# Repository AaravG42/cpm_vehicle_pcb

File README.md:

View this project on [CADLAB.io](https://cadlab.io/project/29694). 

# cpm_vehicle_pcb

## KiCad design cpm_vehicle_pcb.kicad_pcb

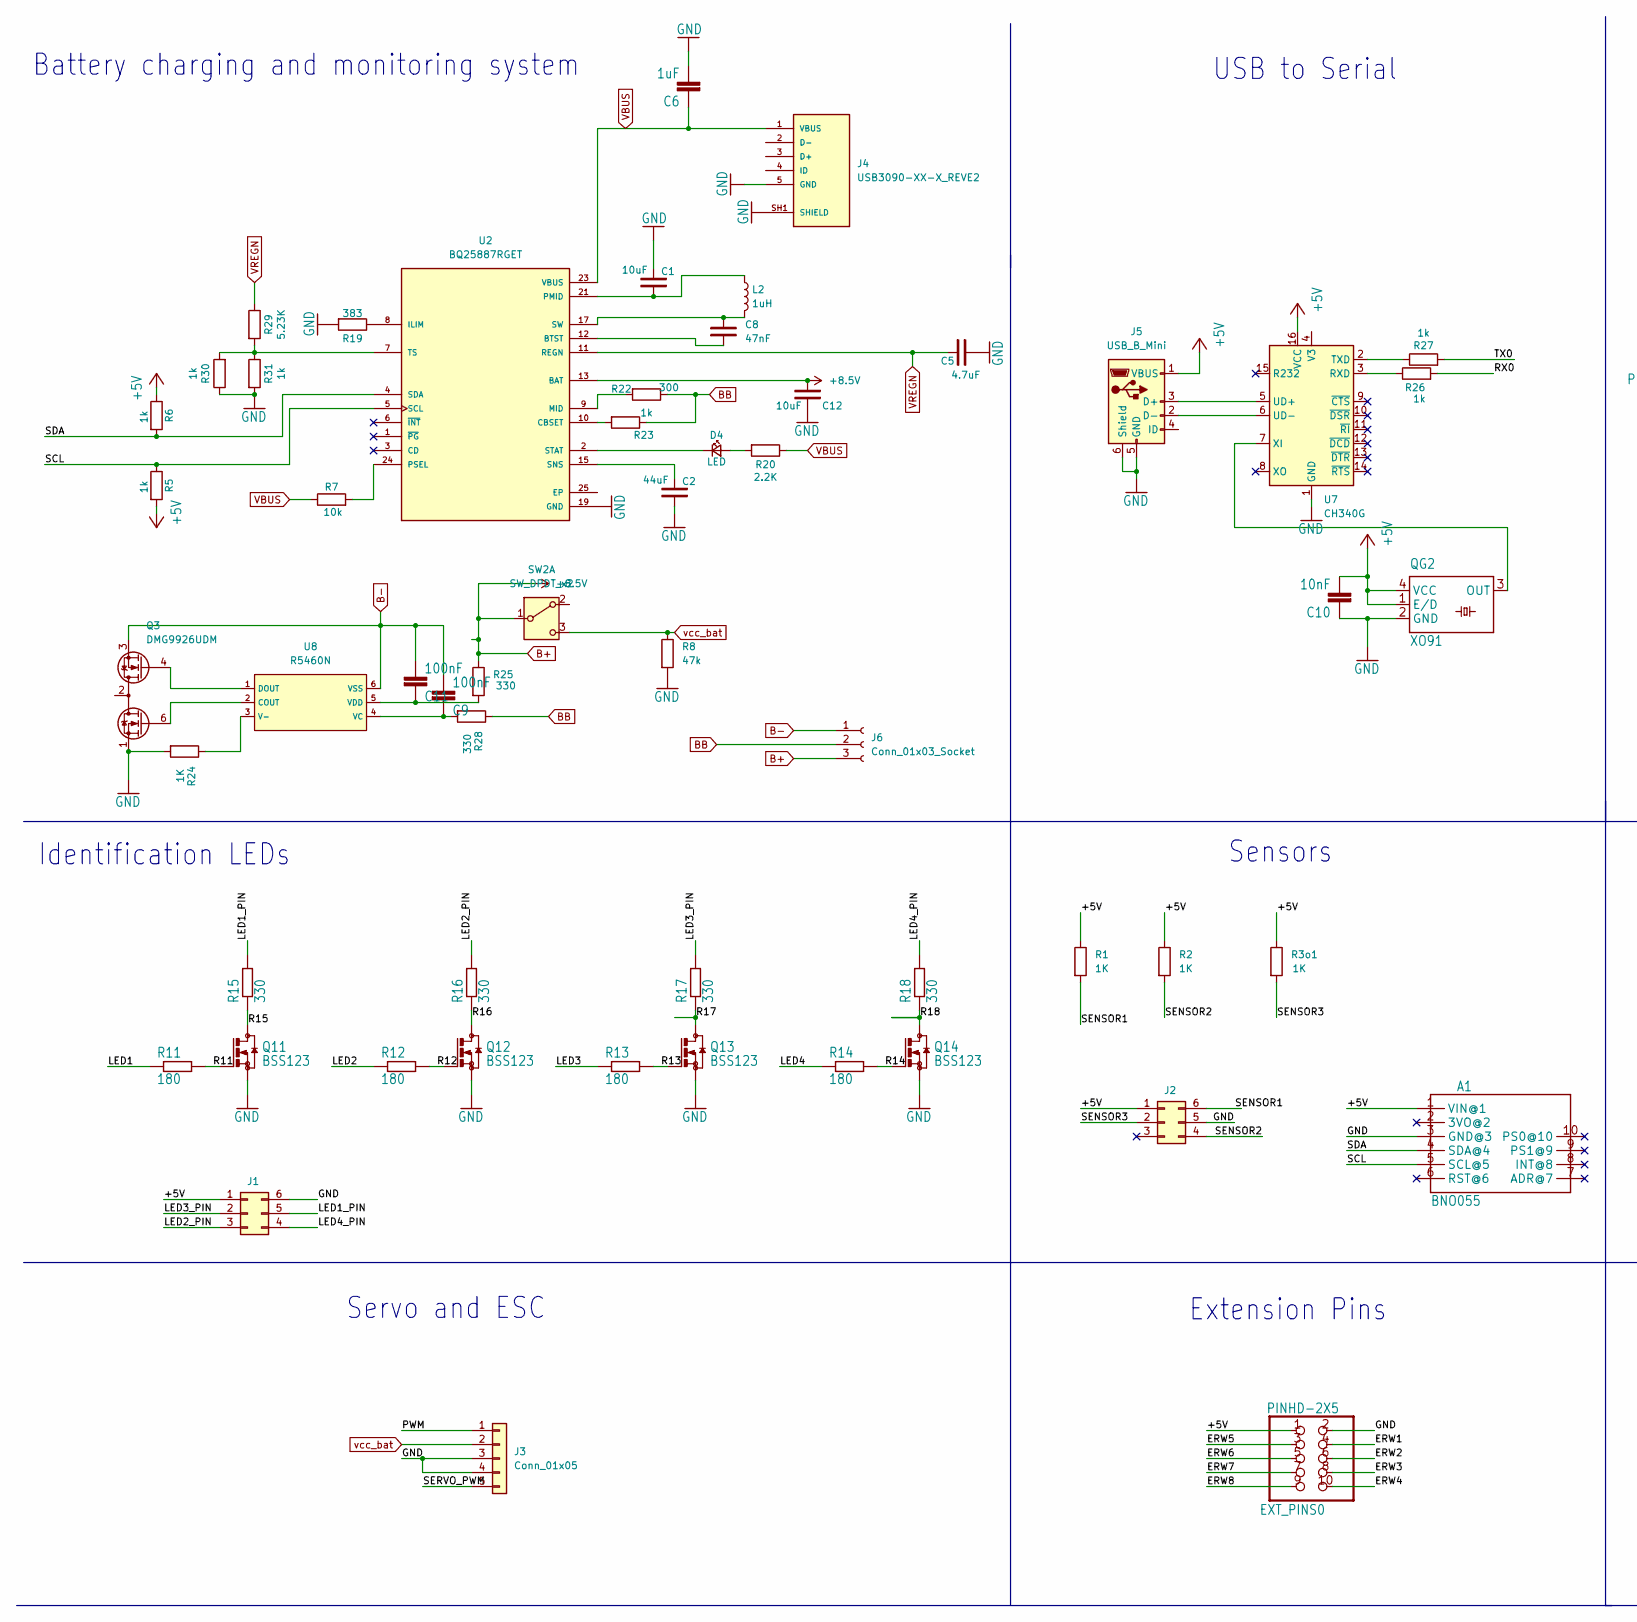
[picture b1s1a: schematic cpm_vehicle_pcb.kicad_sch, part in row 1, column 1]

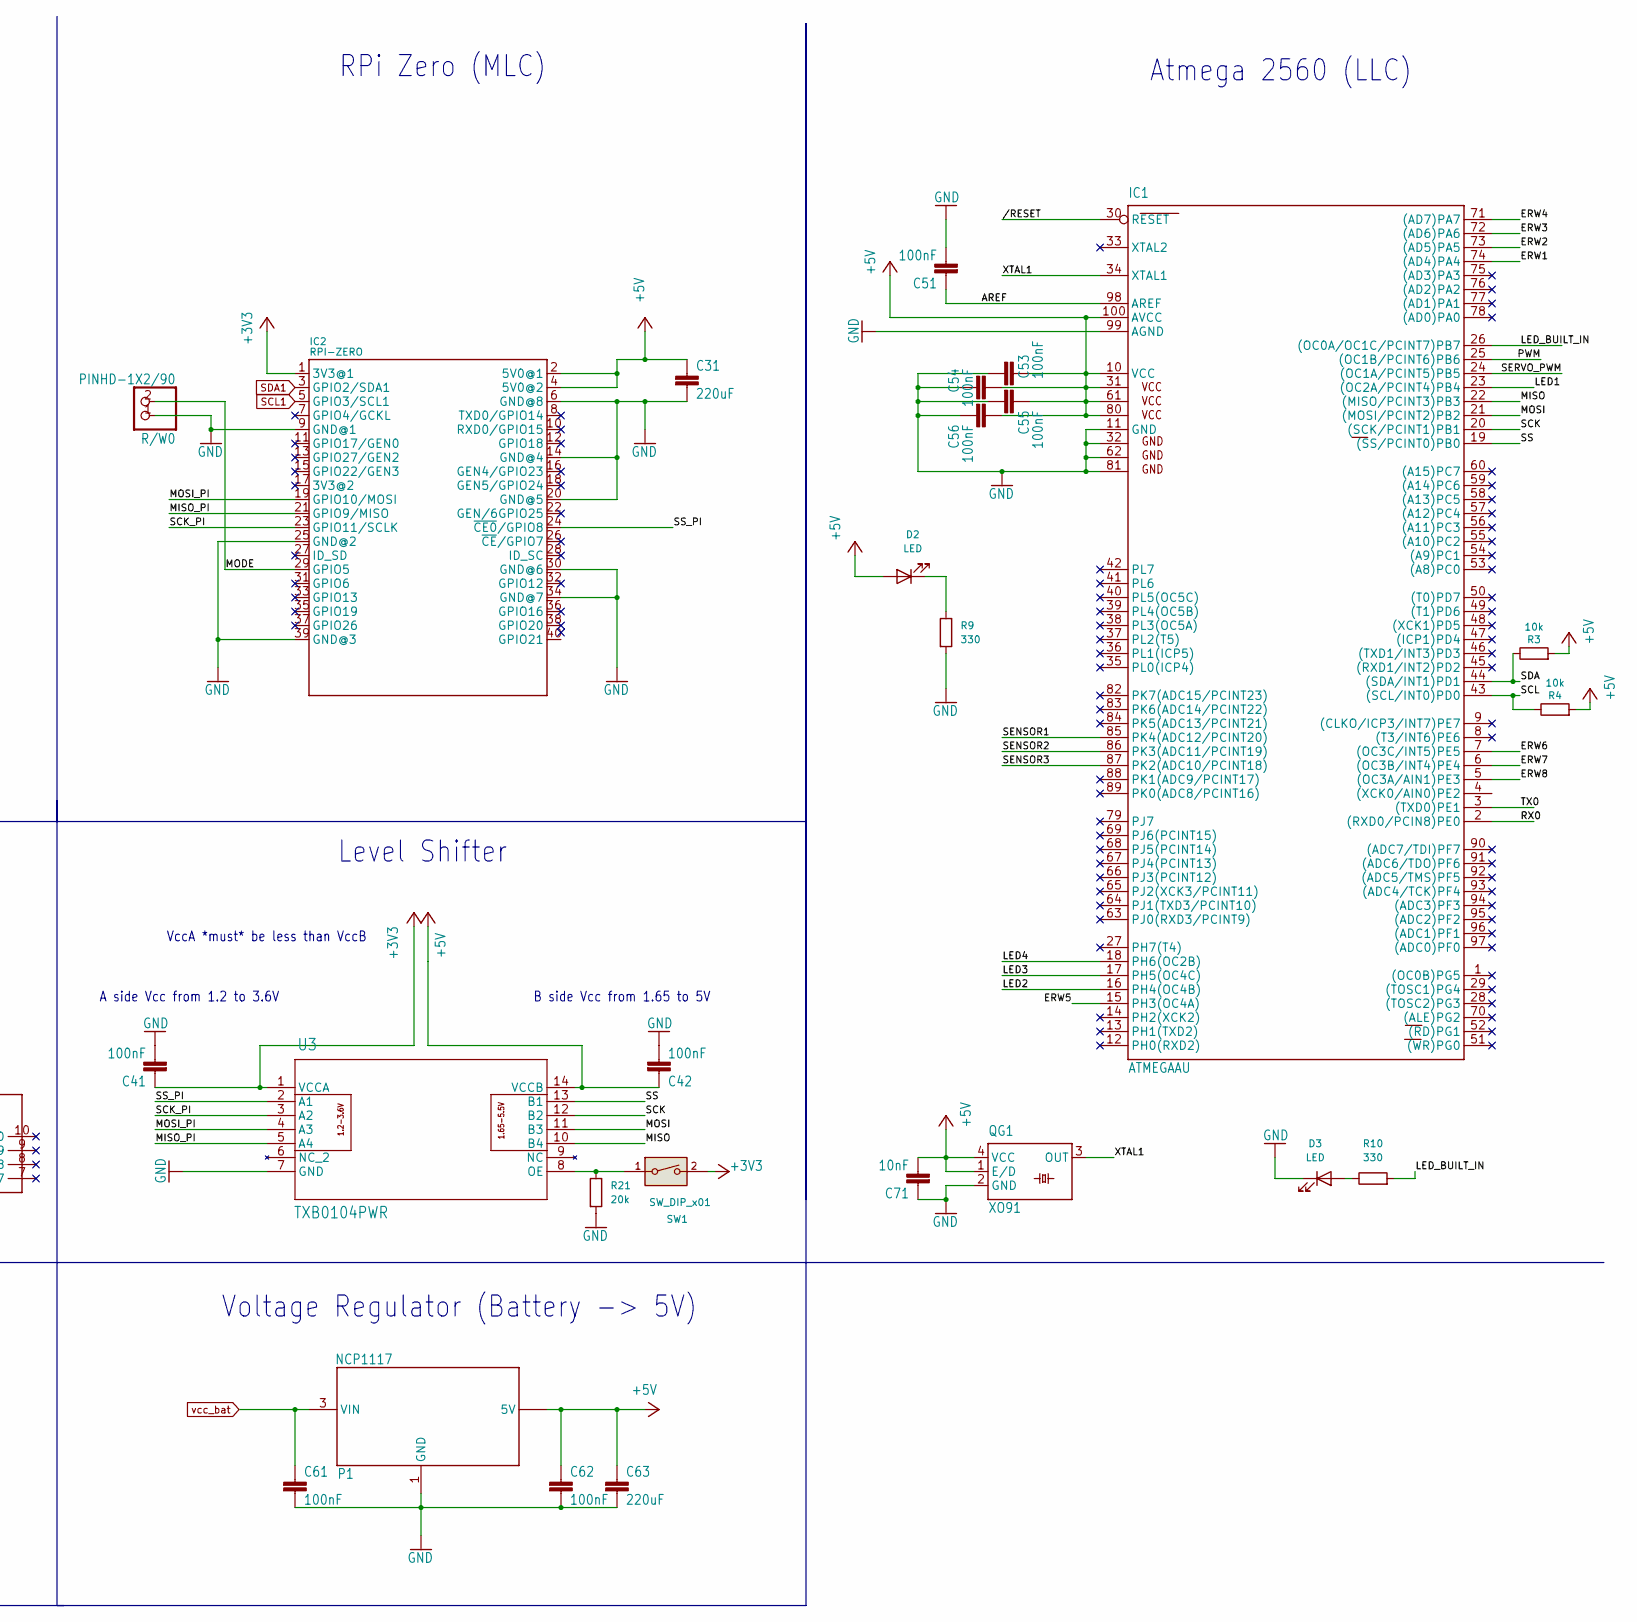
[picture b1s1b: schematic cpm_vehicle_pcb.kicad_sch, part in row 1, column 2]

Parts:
A1: BNO055; BNO055_IMU
C1, C12: 10uF; C0805_10681391
C2: 44uF; C0805_10681391
C5: 4.7uF; C0805_10681391
C6: 1uF; C0805_10681391
C8: 47nF; C0805_10681391
C9, C11, C41, C42, C51, C53, C54, C55, C56, C61, C62: 100nF; C0805_10681391
C10, C71: 10nF; C0805_10681391
C31, C63: 220uF; C_1206_3216Metric
D2, D3, D4: LED; LED_0805_2012Metric
EXT_PINS0: PINHD-2X5; 2X05_EXT_PINS
IC1: ATMEGAAU; TQFP100_atmega2560
IC2: RPI-ZERO; rpi_zero_w
J1, J2: Conn_02x03_Counter_Clockwise; HARWIN_M20-9980346
J3: Conn_01x05; PinHeader_1x05_P2.54mm_Horizontal
J4: USB3090-XX-X_REVE2; GCT_USB3090-XX-X_REVE2; PARTREV E2
J5: USB_B_Mini; USB_Mini-B_AdamTech_MUSB-B5-S-VT-TSMT-1_SMD_Vertical
J6: Conn_01x03_Socket; PinSocket_1x03_P2.54mm_Horizontal
L2: 1uH; L_7.3x7.3_H3.5
P1: NCP1117; SOT223_ncp1117
Q3: DMG9926UDM; SOT-23-6
Q11, Q12, Q13, Q14: BSS123; SOT23_NMOS
QG1, QG2: XO91; SM77H_crystal_oscillator
R1, R2, R3o1, R24: 1K; R_0603_1608Metric
R3, R4, R7: 10k; R_0603_1608Metric
R5, R6, R23, R26, R27, R30, R31: 1k; R_0603_1608Metric
R8: 47k; R_0603_1608Metric
R9, R10, R15, R16, R17, R18, R25, R28: 330; R_0603_1608Metric
R11, R12, R13, R14: 180; R_0603_1608Metric
R19: 383; R_0603_1608Metric
R20: 2.2K; R_0603_1608Metric
R21: 20k; R_0603_1608Metric
R22: 300; R_0603_1608Metric
R29: 5.23K; R_0603_1608Metric
R/W0: PINHD-1X2/90; 1X02_90_rpi
SW1: SW_DIP_x01; SW_DIP_SPSTx01_Slide_9.78x4.72mm_W8.61mm_P2.54mm
SW2: SW_DPDT_x2; SW_Slide-03_Wuerth-WS-SLTV_10x2.5x6.4_P2.54mm
U2: BQ25887RGET; QFN50P400X400X100-25N; PARTREV B
U3: TXB0104PWR
U7: CH340G; SOIC-16_3.9x9.9mm_P1.27mm
U8: R5460N; SOT-23-6_L2.9-W1.6-P0.95-LS2.8-BL; Part TP4057-42-SOT26-R; LCSC C12044

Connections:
+3V3: C41.1, IC2.1 (3V3@1), SW1.2, U3.1 (VCCA)
+5V: A1.1 (VIN@1), C10.2, C31.1, C42.1, C53.1, C54.1, C55.1, C56.1, C62.1, C63.1, C71.2, D2.2 (A), EXT_PINS0.1, IC1.10 (VCC), IC1.31 (VCC1), IC1.61 (VCC2), IC1.80 (VCC3), IC1.100 (AVCC), IC2.2 (5V0@1), IC2.4 (5V0@2), J1.1, J2.1, J5.1 (VBUS), P1.2 (5V), P1.4 (5V), QG1.1 (E/D), QG1.4 (VCC), QG2.1 (E/D), QG2.4 (VCC), R1.1, R2.1, R3.2, R3o1.1, R4.2, R5.2, R6.1, U3.14 (VCCB), U7.16 (VCC)
/AREF: C51.1, IC1.98 (AREF)
/ERW1: EXT_PINS0.4, IC1.74 ((AD4)PA4)
/ERW2: EXT_PINS0.6, IC1.73 ((AD5)PA5)
/ERW3: EXT_PINS0.8, IC1.72 ((AD6)PA6)
/ERW4: EXT_PINS0.10, IC1.71 ((AD7)PA7)
/ERW5: EXT_PINS0.3, IC1.15 (PH3(OC4A))
/ERW6: EXT_PINS0.5, IC1.7 ((OC3C/INT5)PE5)
/ERW7: EXT_PINS0.7, IC1.6 ((OC3B/INT4)PE4)
/ERW8: EXT_PINS0.9, IC1.5 ((OC3A/AIN1)PE3)
/LED1: IC1.23 ((OC2A/PCINT4)PB4), R11.1
/LED1_PIN: J1.5, R15.2
/LED2: IC1.16 (PH4(OC4B)), R12.1
/LED2_PIN: J1.3, R16.2
/LED3: IC1.17 (PH5(OC4C)), R13.1
/LED3_PIN: J1.2, R17.2
/LED4: IC1.18 (PH6(OC2B)), R14.1
/LED4_PIN: J1.4, R18.2
/LED_BUILT_IN: IC1.26 ((OC0A/OC1C/PCINT7)PB7), R10.2
/MISO: IC1.22 ((MISO/PCINT3)PB3), U3.10 (B4)
/MISO_PI: IC2.21 (GPIO9/MISO), U3.5 (A4)
/MODE: IC2.29 (GPIO5), R/W0.2
/MOSI: IC1.21 ((MOSI/PCINT2)PB2), U3.11 (B3)
/MOSI_PI: IC2.19 (GPIO10/MOSI), U3.4 (A3)
/PWM: IC1.25 ((OC1B/PCINT6)PB6), J3.1
/R11: Q11.1 (G), R11.2
/R12: Q12.1 (G), R12.2
/R13: Q13.1 (G), R13.2
/R14: Q14.1 (G), R14.2
/R15: Q11.3 (D), R15.1
/R16: Q12.3 (D), R16.1
/R17: Q13.3 (D), R17.1
/R18: Q14.3 (D), R18.1
/RX0: IC1.2 ((RXD0/PCIN8)PE0), R26.2
/SCK: IC1.20 ((SCK/PCINT1)PB1), U3.12 (B2)
/SCK_PI: IC2.23 (GPIO11/SCLK), U3.3 (A2)
/SCL: A1.5 (SCL@5), IC1.43 ((SCL/INT0)PD0), R4.1, R5.1, U2.5 (SCL)
/SDA: A1.4 (SDA@4), IC1.44 ((SDA/INT1)PD1), R3.1, R6.2, U2.4 (SDA)
/SENSOR1: IC1.85 (PK4(ADC12/PCINT20)), J2.6, R1.2
/SENSOR2: IC1.86 (PK3(ADC11/PCINT19)), J2.4, R2.2
/SENSOR3: IC1.87 (PK2(ADC10/PCINT18)), J2.2, R3o1.2
/SERVO_PWM: IC1.24 ((OC1A/PCINT5)PB5), J3.5
/SS: IC1.19 ((SS/PCINT0)PB0), U3.13 (B1)
/SS_PI: IC2.24 (~CE0/GPIO8), U3.2 (A1)
/TX0: IC1.3 ((TXD0)PE1), R27.2
/XTAL1: IC1.34 (XTAL1), QG1.3 (OUT)
//RESET: IC1.30 (RESET)
B+: C12.1, J6.3, R25.1, SW2.1 (B), U2.13 (BAT), U2.14 (BAT)
B-: C9.2, C11.2, J6.1, Q3.3 (S2), U8.6 (VSS)
BB: J6.2, R22.1, R23.1, R28.1
GND: A1.3 (GND@3), C1.1, C2.2, C5.2, C6.2, C10.1, C12.2, C31.2, C41.2, C42.2, C51.2, C53.2, C54.2, C55.2, C56.2, C61.2, C62.2, C63.2, C71.1, D3.1 (K), EXT_PINS0.2, IC1.11 (GND), IC1.32 (GND1), IC1.62 (GND2), IC1.81 (GND3), IC1.99 (AGND), IC2.6 (GND@8), IC2.9 (GND@1), IC2.14 (GND@4), IC2.20 (GND@5), IC2.25 (GND@2), IC2.30 (GND@6), IC2.34 (GND@7), IC2.39 (GND@3), J1.6, J2.5, J3.3, J3.4, J4.5 (GND), J4.SH1 (SHIELD), J4.SH2 (SHIELD), J4.SH3 (SHIELD), J4.SH4 (SHIELD), J5.5 (GND), J5.6 (Shield), P1.1 (GND), Q3.1 (D1), Q11.2 (S), Q12.2 (S), Q13.2 (S), Q14.2 (S), QG1.2 (GND), QG2.2 (GND), R8.2, R9.2, R19.2, R21.2, R24.2, R30.1, R31.2, R/W0.1, U2.19 (GND), U2.20 (GND), U3.7 (GND), U7.1 (GND)
unnamed: C2.1, U2.15 (SNS), U2.16 (SNS)
unnamed: D2.1 (K), R9.1
unnamed: D3.2 (A), R10.1
unnamed: D4.2 (A), R20.2
unnamed: D4.1 (K), U2.2 (STAT)
unnamed: J5.3 (D+), U7.5 (UD+)
unnamed: J5.2 (D-), U7.6 (UD-)
unnamed: Q3.6 (G1), U8.2 (COUT)
unnamed: Q3.4 (G2), U8.1 (DOUT)
unnamed: Q3.2 (S1/D2), Q3.5 (S1/D2)
unnamed: QG2.3 (OUT), U7.7 (XI)
unnamed: C8.1, U2.12 (BTST)
unnamed: R23.2, U2.10 (CBSET)
unnamed: U2.25 (EP), U2.25_1 (EP), U2.25_2 (EP), U2.25_3 (EP), U2.25_4 (EP), U2.25_5 (EP)
unnamed: R19.1, U2.8 (ILIM)
unnamed: R22.2, U2.9 (MID)
unnamed: R7.2, U2.24 (PSEL)
unnamed: R29.2, R30.2, R31.1, U2.7 (TS)
unnamed: R21.1, SW1.1, U3.8 (OE)
unnamed: R26.1, U7.3 (RXD)
unnamed: R27.1, U7.2 (TXD)
unnamed: R24.1, U8.3 (V-)
unnamed: C9.1, R28.2, U8.4 (VC)
unnamed: C11.1, R25.2, U8.5 (VDD)
PMID: C1.2, L2.1, U2.21 (PMID), U2.22 (PMID)
SCL1: IC2.5 (GPIO3/SCL1)
SDA1: IC2.3 (GPIO2/SDA1)
SW: C8.2, L2.2, U2.17 (SW), U2.18 (SW)
VBUS: C6.1, J4.1 (VBUS), R7.1, R20.1, U2.23 (VBUS)
VREGN: C5.1, R29.1, U2.11 (REGN)
vcc_bat: C61.1, J3.2, P1.3 (VIN), R8.1, SW2.3 (C)

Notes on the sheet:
Level Shifter
A side Vcc from 1.2 to 3.6V
VccA *must* be less than VccB~{}
Identification LEDs
Sensors
RPi Zero (MLC)
Servo and ESC
Voltage Regulator (Battery -> 5V)
USB to Serial
Extension Pins
Battery charging and monitoring system
B side Vcc from 1.65 to 5V
Atmega 2560 (LLC)

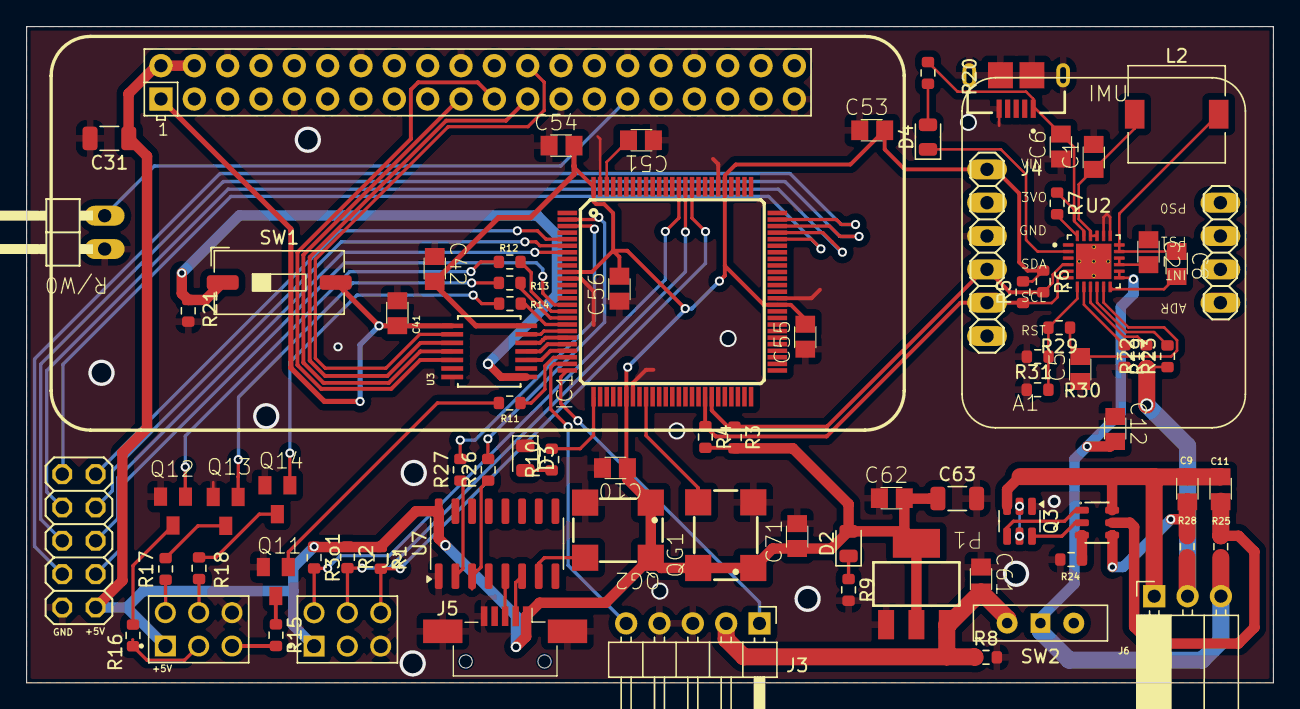
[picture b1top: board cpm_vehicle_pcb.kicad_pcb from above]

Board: 2 copper layers, 95.0 x 50.0 mm, 82 parts (0 on the bottom side), 80 nets.

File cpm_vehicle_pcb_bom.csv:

"Id";"Designator";"Footprint";"Quantity";"Designation";"Supplier and ref";
1;"R2,R3o1,R24,R1";"R_0603_1608Metric";4;"1K";;;
2;"R29";"R_0603_1608Metric";1;"5.23K";;;
3;"A1";"BNO055_IMU";1;"BNO055";;;
4;"SW1";"SW_DIP_SPSTx01_Slide_9.78x4.72mm_W8.61mm_P2.54mm";1;"SW_DIP_x01";;;
5;"R22";"R_0603_1608Metric";1;"300";;;
6;"C9,C56,C55,C61,C51,C53,C41,C11,C54,C42,C62";"C0805_10681391";11;"100nF";;;
7;"J6";"PinSocket_1x03_P2.54mm_Horizontal";1;"Conn_01x03_Socket";;;
8;"Q12,Q11,Q14,Q13";"SOT23_NMOS";4;"BSS123";;;
9;"R4,R7,R3";"R_0603_1608Metric";3;"10k";;;
10;"R8";"R_0603_1608Metric";1;"47k";;;
11;"R26,R5,R23,R30,R6,R27,R31";"R_0603_1608Metric";7;"1k";;;
12;"R15,R25,R9,R28,R10,R17,R18,R16";"R_0603_1608Metric";8;"330";;;
13;"R/W0";"1X02_90_rpi";1;"PINHD-1X2/90";;;
14;"IC1";"TQFP100_atmega2560";1;"ATMEGAAU";;;
15;"D2,D3,D4";"LED_0805_2012Metric";3;"LED";;;
16;"C71,C10";"C0805_10681391";2;"10nF";;;
17;"C63,C31";"C0805_10681391";2;"220uF";;;
18;"J3";"PinHeader_1x05_P2.54mm_Horizontal";1;"Conn_01x05";;;
19;"R13,R12,R11,R14";"R_0603_1608Metric";4;"180";;;
20;"C5";"C0805_10681391";1;"4.7uF";;;
21;"J4";"GCT_USB3090-XX-X_REVE2";1;"USB3090-XX-X_REVE2";;;
22;"QG1,QG2";"SM77H_crystal_oscillator";2;"XO91";;;
23;"C1,C12";"C0805_10681391";2;"10uF";;;
24;"U3";"TXB0104PWR";1;"TXB0104PWR";;;
25;"C2";"C0805_10681391";1;"44uF";;;
26;"SW2";"SW_Slide-03_Wuerth-WS-SLTV_10x2.5x6.4_P2.54mm";1;"SW_DPDT_x2";;;
27;"P1";"SOT223_ncp1117";1;"NCP1117";;;
28;"R19";"R_0603_1608Metric";1;"383";;;
29;"Q3";"SOT-23-6";1;"DMG9926UDM";;;
30;"J1,J2";"HARWIN_M20-9980346";2;"Conn_02x03_Counter_Clockwise";;;
31;"J5";"USB_Mini-B_AdamTech_MUSB-B5-S-VT-TSMT-1_SMD_Vertical";1;"USB_B_Mini";;;
32;"R20";"R_0603_1608Metric";1;"2.2K";;;
33;"U2";"QFN50P400X400X100-25N";1;"BQ25887RGET";;;
34;"EXT_PINS0";"2X05_EXT_PINS";1;"PINHD-2X5";;;
35;"IC2";"rpi_zero_w";1;"RPI-ZERO";;;
36;"C6";"C0805_10681391";1;"1uF";;;
37;"U7";"SOIC-16_3.9x9.9mm_P1.27mm";1;"CH340G";;;
38;"L2";"L_10.4x10.4_H4.8";1;"1uH";;;
39;"C8";"C0805_10681391";1;"47nF";;;
40;"R21";"R_0603_1608Metric";1;"20k";;;
41;"U8";"SOT-23-6_L2.9-W1.6-P0.95-LS2.8-BL";1;"R5460N";;;

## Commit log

2025-10-10 test add to schematic
2025-10-10 test for github dektop with pcb
2025-10-12 schematic of battery management
2025-10-16 usb to serial and some external pin and led circuit changes
2025-10-16 nothing
2025-10-17 Small footprint changes
2025-10-18 Net class defined
2025-10-18 Backlink to CADLAB.io has been added.
2025-10-18 some minute changes
2025-10-19 Battery Protection Routing done
2025-10-19 Some Routing
2025-10-19 Routing 2
2025-10-19 routing2_a
2025-11-18 Added Bq25887
2025-11-19 Schematic BQ25887
2025-11-22 DONE
2025-11-22 some changes
2025-11-23 FinalV_1
2025-12-09 Last Updates
2025-12-09 Final Update ver 2
2025-12-09 Ver2
